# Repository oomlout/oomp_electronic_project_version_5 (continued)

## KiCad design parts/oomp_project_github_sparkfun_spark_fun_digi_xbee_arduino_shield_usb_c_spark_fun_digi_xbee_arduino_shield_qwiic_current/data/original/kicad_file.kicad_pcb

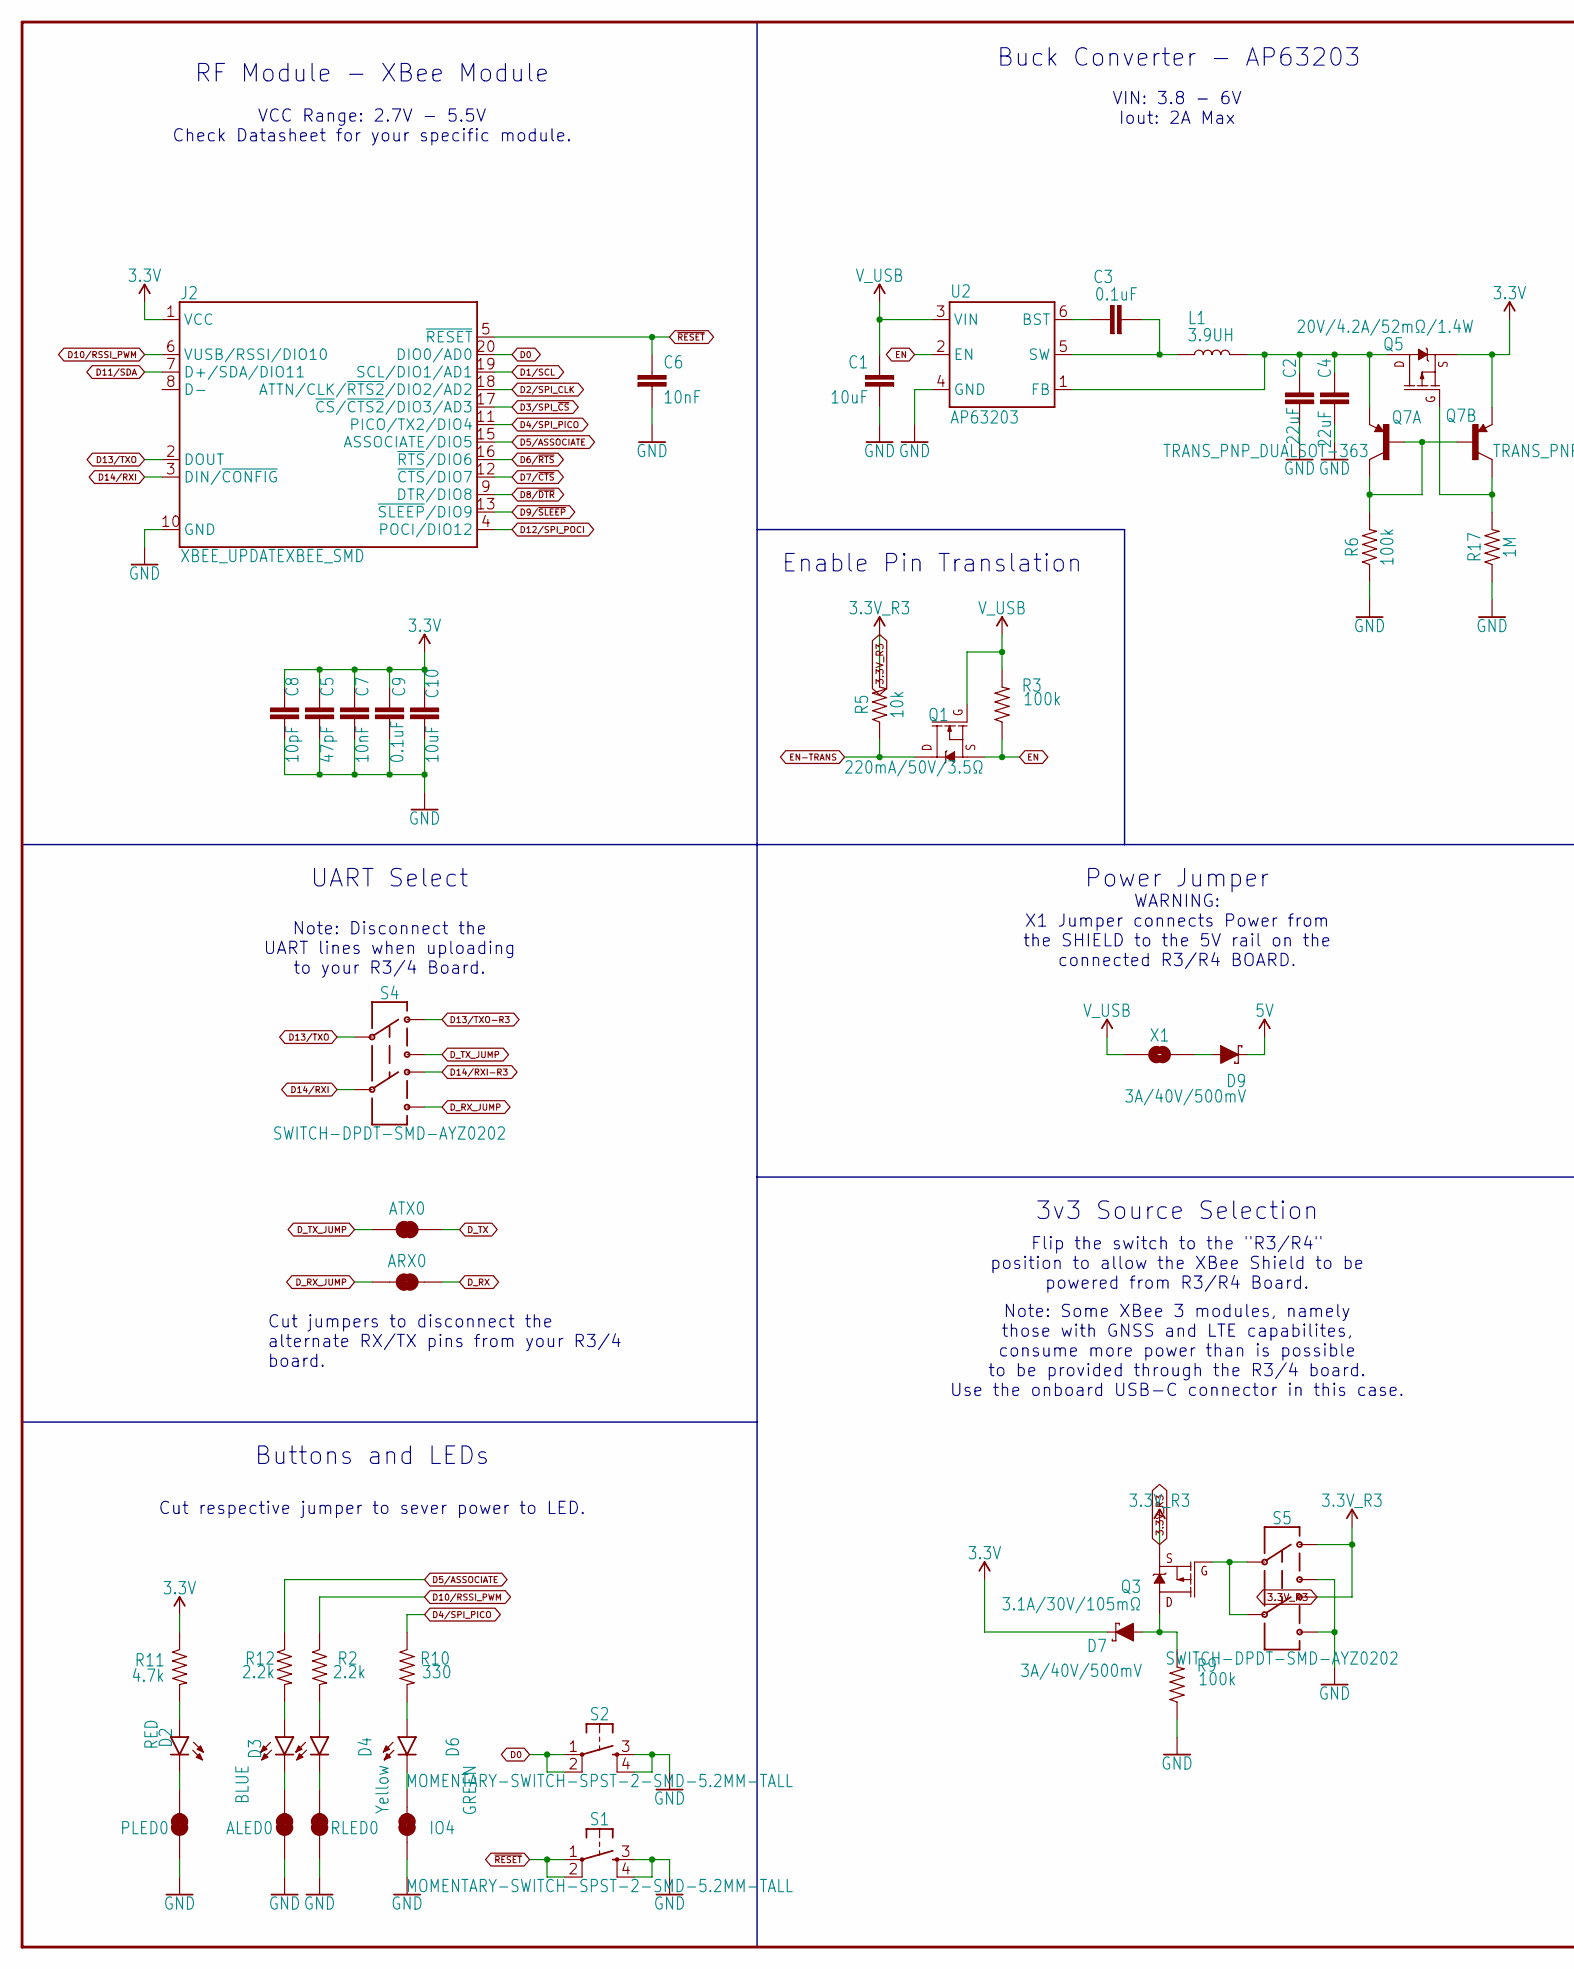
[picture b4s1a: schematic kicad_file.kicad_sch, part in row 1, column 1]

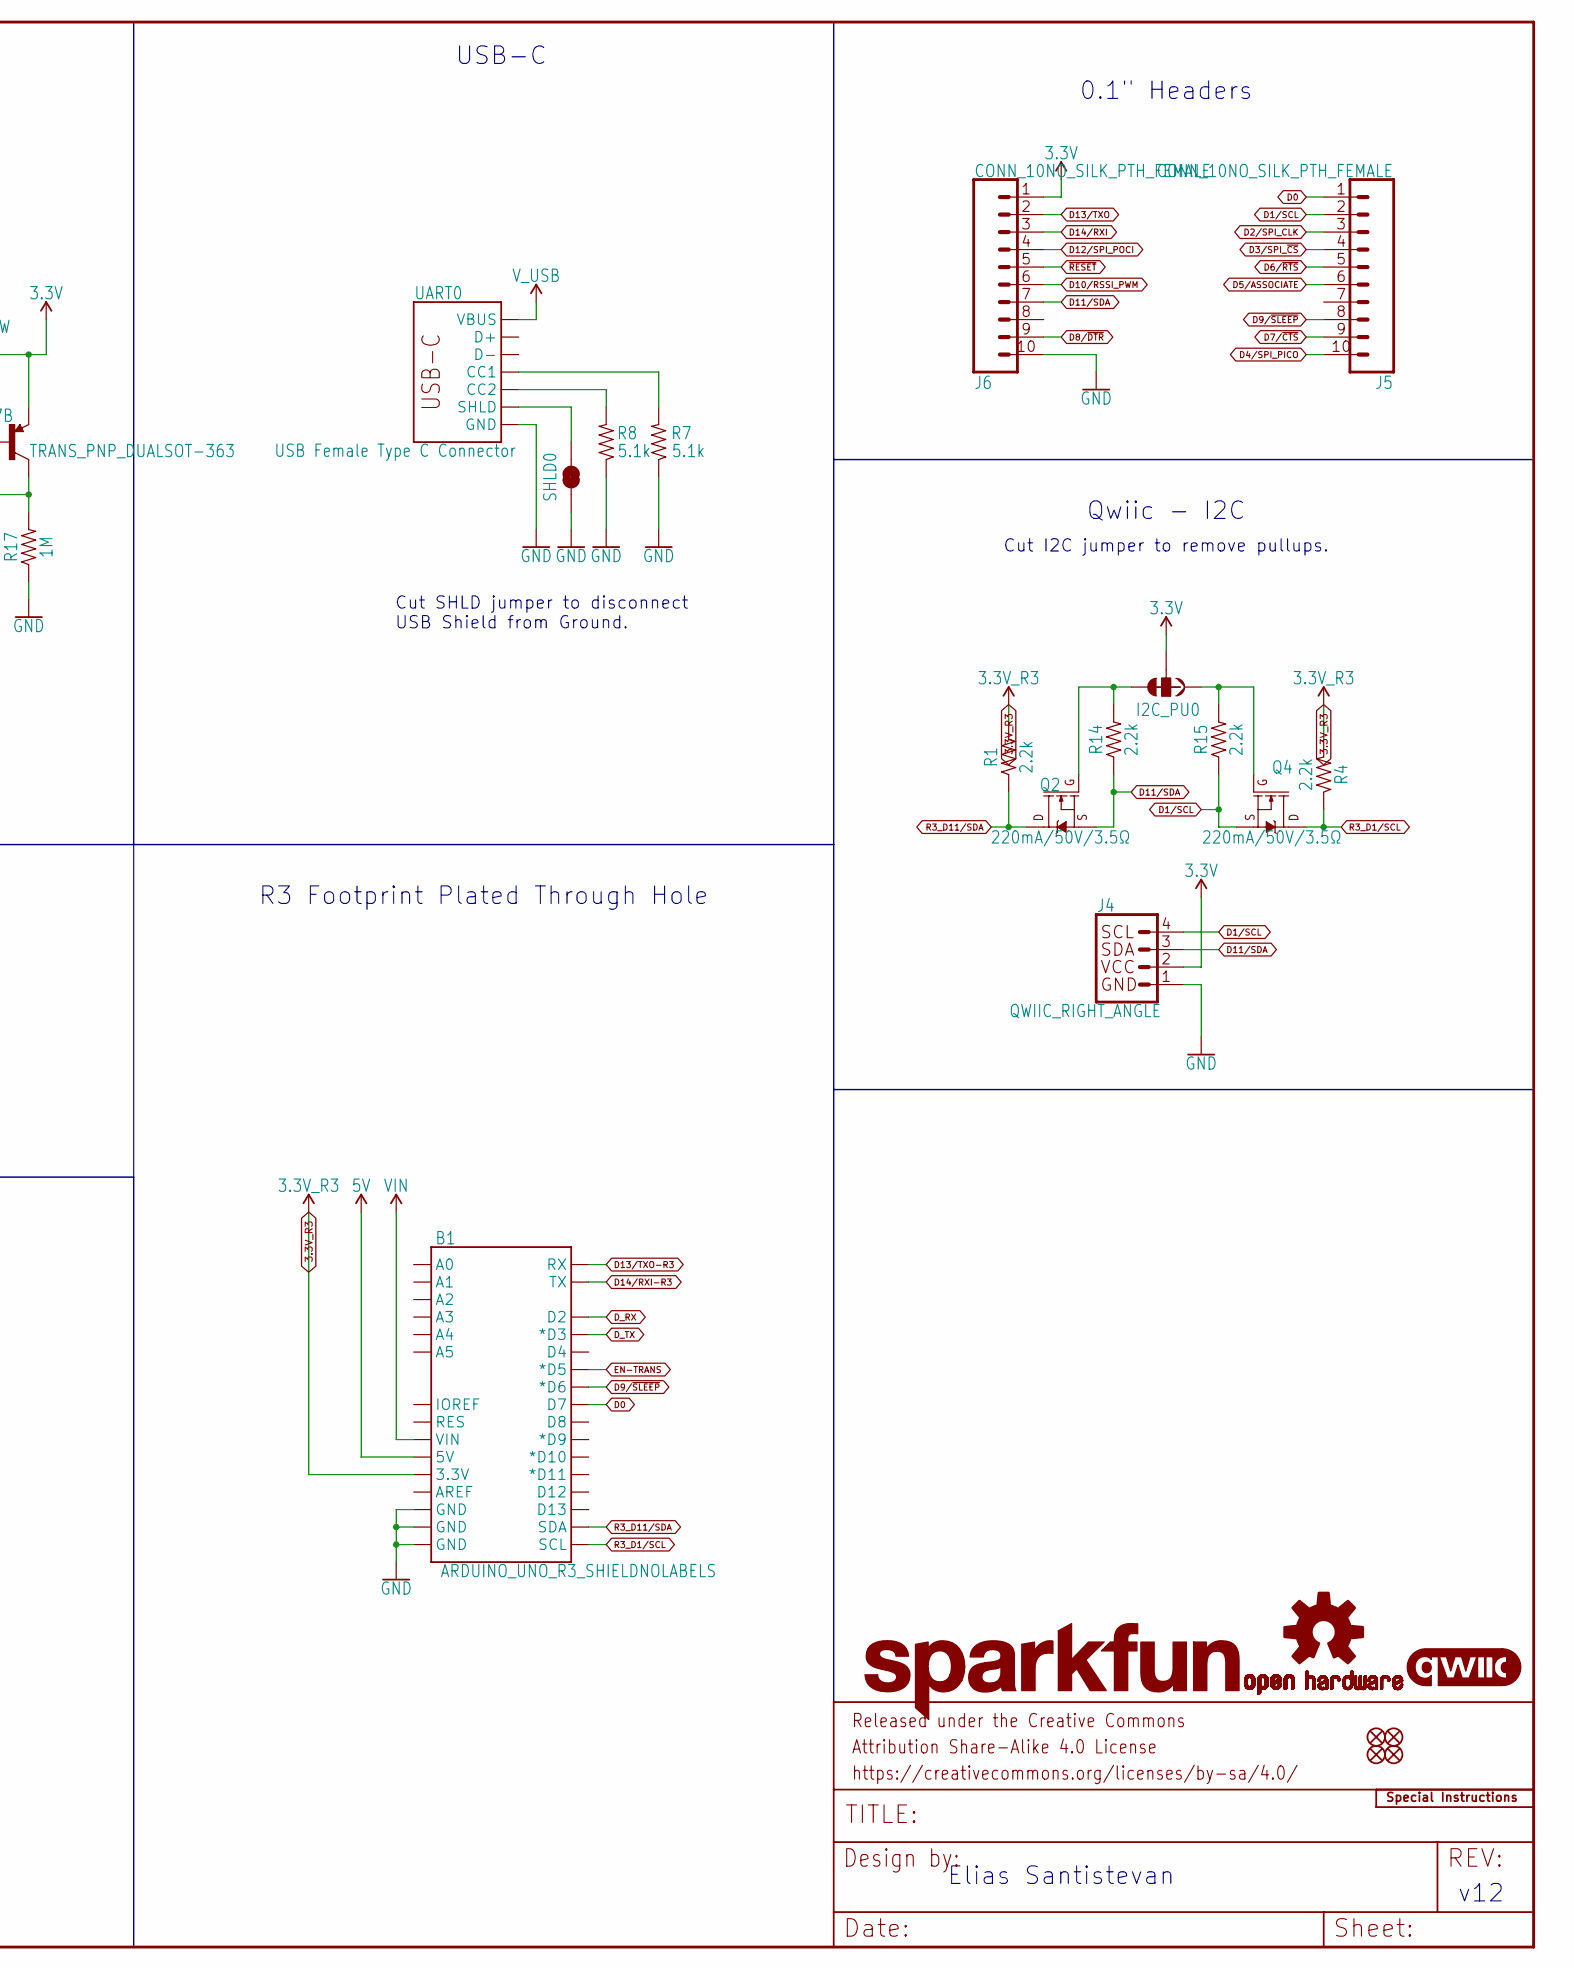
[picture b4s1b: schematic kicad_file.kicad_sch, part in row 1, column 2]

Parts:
ALED0: JUMPER-SMT_2_NC_TRACE_SILK; SMT-JUMPER_2_NC_TRACE_SILK
ARX0: JUMPER-SMT_2_NC_TRACE_SILK; SMT-JUMPER_2_NC_TRACE_SILK
ATX0: JUMPER-SMT_2_NC_TRACE_SILK; SMT-JUMPER_2_NC_TRACE_SILK
B1: ARDUINO_UNO_R3_SHIELDNOLABELS; UNO_R3_SHIELD_NOLABELS
C1: 10uF; 1210
C2, C4: 22uF; 0603
C3, C9: 0.1uF; 0603
C5: 47pF; 0603
C6, C7: 10nF; 0603
C8: 10pF; 0603
C10: 10uF; 0603
D2: RED; LED-0603
D3: BLUE; LED-0603
D4: Yellow; LED-0603
D6: GREEN; LED-0603
D7, D9: 3A/40V/500mV; SMA-DIODE
FD1, FD2, FD3, FD4: FIDUCIAL1X2; FIDUCIAL-1X2
FRAME1: FRAME-LEDGER; CREATIVE_COMMONS
I2C_PU0: JUMPER-SMT_3_2-NC_TRACE_SILK; SMT-JUMPER_3_2-NC_TRACE_SILK
IO4: JUMPER-SMT_2_NC_TRACE_SILK; SMT-JUMPER_2_NC_TRACE_SILK
J2: XBEE_UPDATEXBEE_SMD; XBEE3-SMD
J4: QWIIC_RIGHT_ANGLE; JST04_1MM_RA
J5, J6: CONN_10NO_SILK_PTH_FEMALE; 1X10_NO_SILK
L1: 3.9UH; INDUCTOR_3.9UH
LOGO1: SFE_LOGO_NAMEBLANK; BLANK
LOGO2: OSHW-LOGOS; OSHW-LOGO-S
LOGO3: QWIIC_LOGO_4MM; QWIIC_4MM
LOGO4: SPECIAL_INSTRUCTIONS-ORDERING; ORDERING_INSTRUCTIONS
PLED0: JUMPER-SMT_2_NC_TRACE_SILK; SMT-JUMPER_2_NC_TRACE_SILK
Q1, Q2, Q4: 220mA/50V/3.5Ω; SOT23-3
Q3: 3.1A/30V/105mΩ; SOT23-3
Q5: 20V/4.2A/52mΩ/1.4W; SOT23-3
Q7: TRANS_PNP_DUALSOT-363; SOT363_PHILIPS
R1, R2, R4, R12, R14, R15: 2.2k; 0603
R3, R6, R9: 100k; 0603
R5: 10k; 0603
R7, R8: 5.1k; 0603
R10: 330; 0603
R11: 4.7k; 0603
R17: 1M; 0603
RLED0: JUMPER-SMT_2_NC_TRACE_SILK; SMT-JUMPER_2_NC_TRACE_SILK
S1, S2: MOMENTARY-SWITCH-SPST-2-SMD-5.2MM-TALL; TACTILE_SWITCH_SMD_5.2MM
S4, S5: SWITCH-DPDT-SMD-AYZ0202; SWITCH_DPDT_SMD_AYZ0202
SHLD0: JUMPER-SMT_2_NC_TRACE_SILK; SMT-JUMPER_2_NC_TRACE_SILK
U2: AP63203; SOT23-6
UART0: USB Female Type C Connector; USB-C-16P-4LAYER-ISOLATED
X1: JUMPER-SMT_2_NO_SILK; SMT-JUMPER_2_NO_SILK

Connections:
3.3V: C5.1, C7.1, C8.1, C9.1, C10.1, D7.C, I2C_PU0.2, J2.1 (VCC), J4.2, J6.1, Q5.2 (S), Q7.4 (E), R11.1
3.3V_R3: B1.3.3V, Q3.2 (S), R1.2, R4.2, R5.2, S5.3, S5.6
3.3V_VREG: C2.1, C4.1, L1.P$2 (2), Q5.3 (D), Q7.1 (E), U2.1 (FB)
5V: B1.5V, D9.C
D0: B1.D7, J2.20 (DIO0/AD0), J5.1, S2.1, S2.2
D1/SCL: J2.19 (SCL/DIO1/AD1), J4.4, J5.2, Q4.2 (S), R15.1
D2/SPI_CLK: J2.18 (ATTN/CLK/~RTS2/DIO2/AD2), J5.3
D3/SPI_~CS: J2.17 (~CS/~CTS2/DIO3/AD3), J5.4
D4/SPI_PICO: J2.11 (PICO/TX2/DIO4), J5.10, R10.1
D5/ASSOCIATE: J2.15 (ASSOCIATE/DIO5), J5.6, R12.1
D6/~RTS: J2.16 (~RTS/DIO6), J5.5
D7/~CTS: J2.12 (~CTS/DIO7), J5.9
D8/~DTR: J2.9 (DTR/DIO8), J6.9
D9/~SLEEP: B1.D6 (*D6), J2.13 (~SLEEP/DIO9), J5.8
D10/RSSI_PWM: J2.6 (VUSB/RSSI/DIO10), J6.6, R2.1
D11/SDA: J2.7 (D+/SDA/DIO11), J4.3, J6.7, Q2.2 (S), R14.1
D12/SPI_POCI: J2.4 (POCI/DIO12), J6.4
D13/TXO: J2.2 (DOUT), J6.2, S4.2
D13/TXO-R3: B1.RX, S4.3
D14/RXI: J2.3 (DIN/~CONFIG), J6.3, S4.5
D14/RXI-R3: B1.TX, S4.6
D_RX: ARX0.2, B1.D2
D_RX_JUMP: ARX0.1, S4.4
D_TX: ATX0.2, B1.D3 (*D3)
D_TX_JUMP: ATX0.1, S4.1
EN: Q1.2 (S), R3.1, U2.2 (EN)
EN-TRANS: B1.D5 (*D5), Q1.3 (D), R5.1
GND: ALED0.1, B1.GND@0 (GND), B1.GND@1 (GND), B1.GND@2 (GND), C1.2, C2.2, C4.2, C5.2, C6.2, C7.2, C8.2, C9.2, C10.2, IO4.1, J2.10 (GND), J4.1, J6.10, PLED0.1, R6.1, R7.1, R8.1, R9.1, R17.1, RLED0.1, S1.3, S1.4, S2.3, S2.4, S5.1, S5.4, SHLD0.1, U2.4 (GND), UART0.GND, UART0.GND2 (GND)
unnamed: C3.1, U2.6 (BST)
unnamed: D4.A, R2.2
unnamed: D4.C, RLED0.2
unnamed: D6.A, R10.2
unnamed: R8.2, UART0.B5 (CC2)
unnamed: R7.2, UART0.A5 (CC1)
unnamed: D2.A, R11.2
unnamed: C3.2, L1.P$1 (1), U2.5 (SW)
unnamed: D9.A, X1.2
unnamed: I2C_PU0.1, Q4.1 (G), R15.2
unnamed: I2C_PU0.3, Q2.1 (G), R14.2
unnamed: D3.A, R12.2
unnamed: D7.A, Q3.3 (D), R9.2
unnamed: D6.C, IO4.2
unnamed: Q7.2 (B), Q7.5 (B), Q7.6 (C), R6.2
unnamed: Q5.1 (G), Q7.3 (C), R17.2
unnamed: ALED0.2, D3.C
unnamed: D2.C, PLED0.2
unnamed: Q3.1 (G), S5.2, S5.5
R3_D1/SCL: B1.SCL, Q4.3 (D), R4.1
R3_D11/SDA: B1.SDA, Q2.3 (D), R1.1
SHLD: SHLD0.2, UART0.SHLD1 (SHLD), UART0.SHLD2 (SHLD), UART0.SHLD3 (SHLD), UART0.SHLD4 (SHLD), UART0.SHLD5 (SHLD), UART0.SHLD6 (SHLD), UART0.SHLD7 (SHLD), UART0.SHLD8 (SHLD)
VIN: B1.VIN
V_USB: C1.1, Q1.1 (G), R3.2, U2.3 (VIN), UART0.VBUS1 (VBUS), UART0.VBUS2 (VBUS), X1.1
~RESET: C6.1, J2.5 (~RESET), J6.5, S1.1, S1.2

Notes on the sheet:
USB-C
0.1" Headers
R3 Footprint Plated Through Hole
Flip the switch to the "R3/R4" position to allow the XBee Shield to be powered from R3/R4 Board.
Cut respective jumper to sever power to LED.
Buck Converter - AP63203
Cut jumpers to disconnect the alternate RX/TX pins from your R3/4 board.
Note: Disconnect the UART lines when uploading to your R3/4 Board.
UART Select
VIN: 3.8 - 6V Iout: 2A Max
Power Jumper
Buttons and LEDs
3v3 Source Selection
Note: Some XBee 3 modules, namely those with GNSS and LTE capabilites, consume more power than is possible to be provided through the R3/4 board. Use the onboard USB-C connector in this case.
RF Module - XBee Module
Enable Pin Translation
Cut I2C jumper to remove pullups.
v12
Elias Santistevan
Qwiic - I2C
VCC Range: 2.7V - 5.5V Check Datasheet for your specific module.
WARNING: X1 Jumper connects Power from the SHIELD to the 5V rail on the connected R3/R4 BOARD.
Cut SHLD jumper to disconnect USB Shield from Ground.

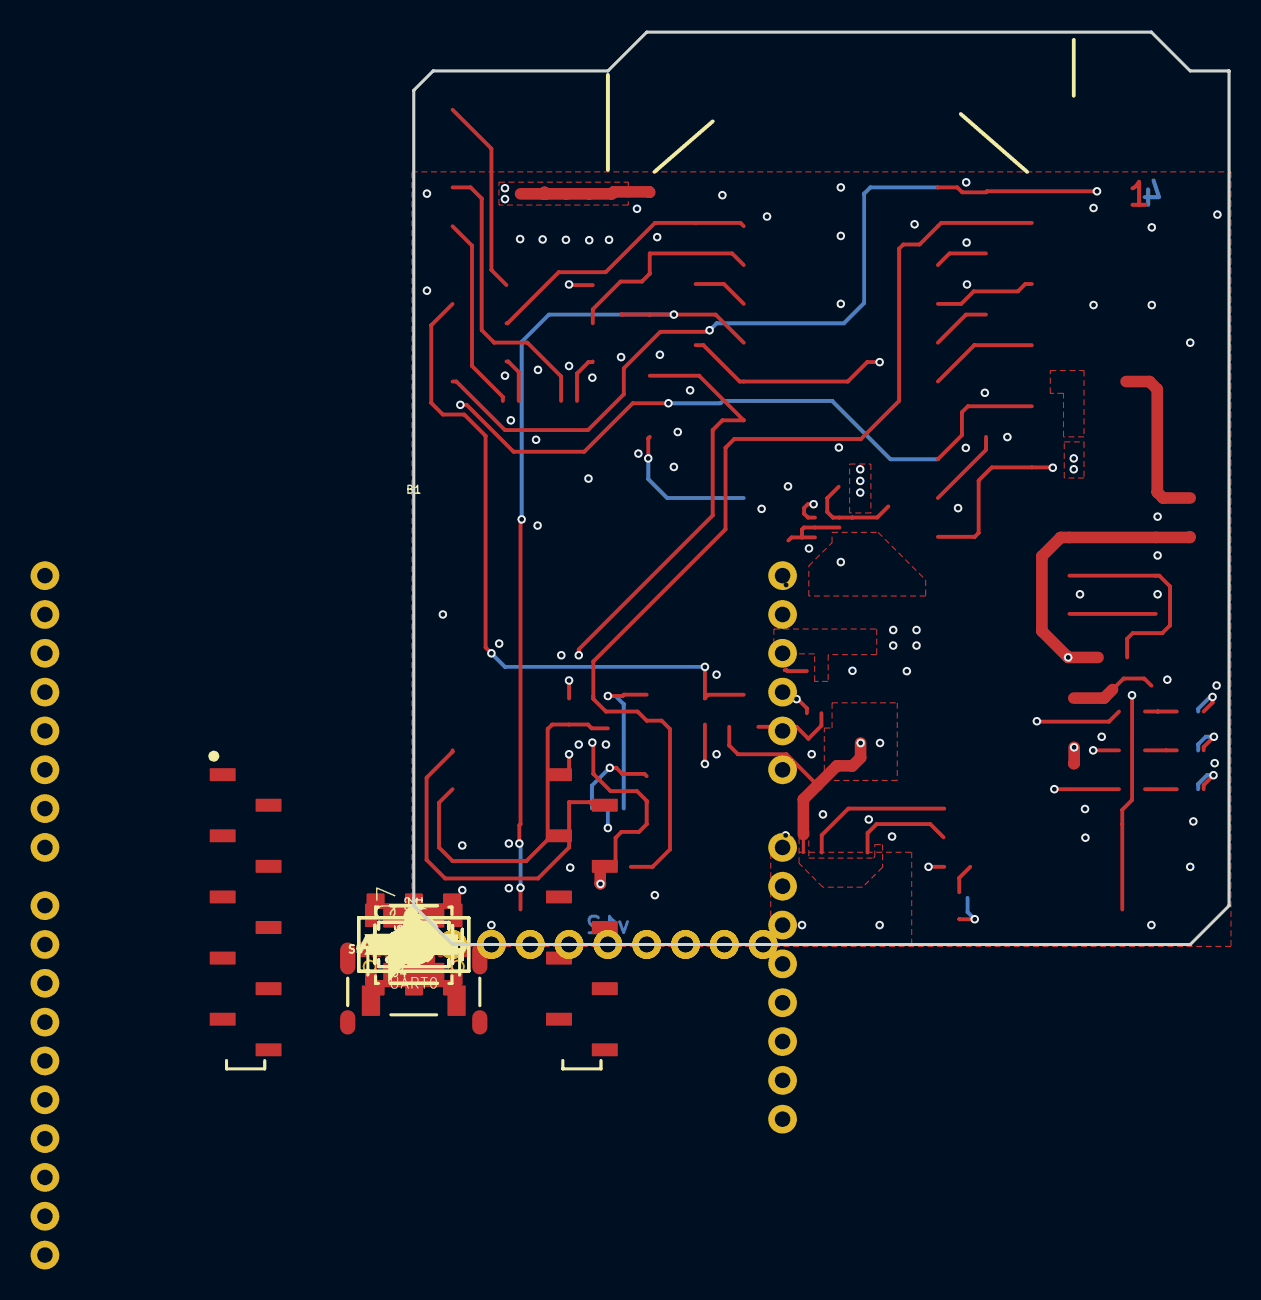
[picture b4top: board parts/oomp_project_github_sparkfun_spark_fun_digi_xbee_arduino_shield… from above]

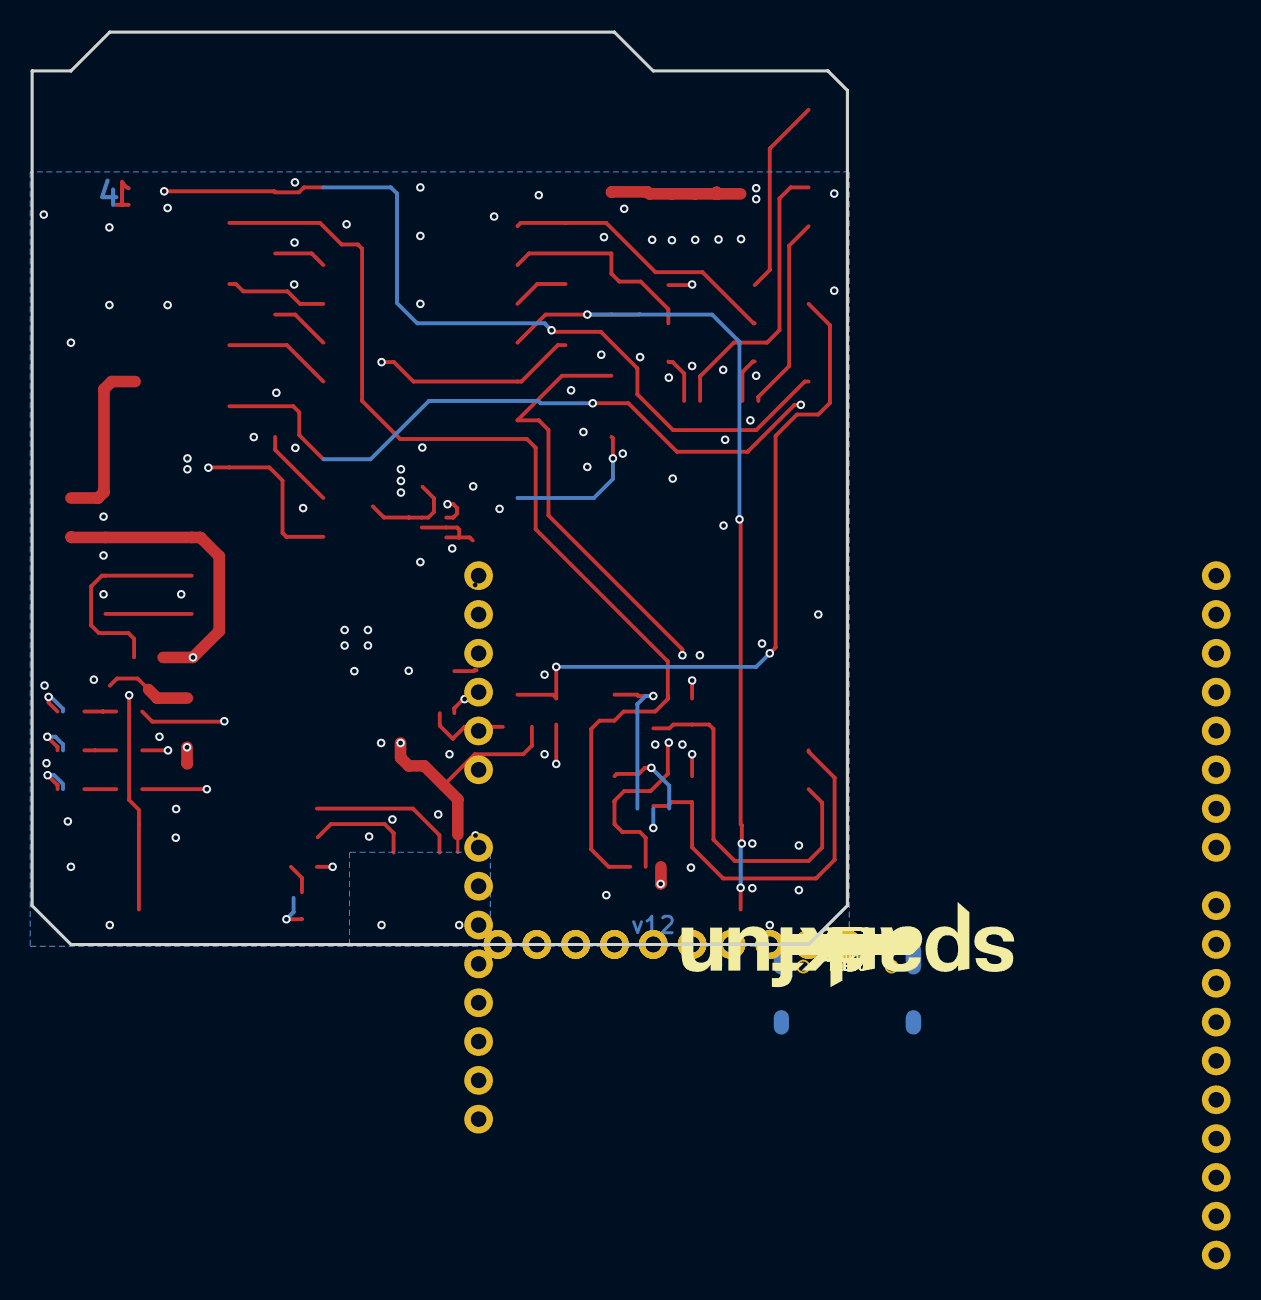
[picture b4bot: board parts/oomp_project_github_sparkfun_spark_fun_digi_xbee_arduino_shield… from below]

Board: 4 copper layers, 53.3 x 59.7 mm, 163 parts (51 on the bottom side), 52 nets.

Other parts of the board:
U$1: RSSI31
U$2: PWR29
U$3, U$56: #SDA#10
U$4: #SHLD#36
U$5, U$9: #NC#1
U$6: #D3#AD3#23
U$7, U$10: #NC#3
U$8: ##DTR##27
U$11: #D1#AD1#8
U$12: ##CTS##28
U$13: #D8##DTR##27
U$14: #RSSI#D10#17
U$15: #SDA#D11#9
U$16: ##RST##15
U$17: #POCI#D12#24
U$18: #RXI#D14#15
U$19: #D2#AD2#19
U$20: #D6##RTS##25
U$21, U$32: #TXO#8
U$22: #TXO#D13#13
U$23: VIN5
U$24: #SCL#7
U$25, U$29, U$41, U$50, U$53, U$63, U$76, U$82: #GND#0
U$26: #I2C#33
U$27, U$33: #RXI#7
U$28: DRX52
U$30: #RST#30
U$31: #PICO#27
U$34: DTX53
U$35: #D5#ASSOC#25
U$36: #D9##SLP##28
U$37: #D7##CTS##26
U$38: #D4#PICO#25
U$39, U$66: #5V#5
U$40: D03
U$42: DLINE45
U$43: #X1#10
U$44, U$47, U$77, U$84: #3V3#1
U$45: #POCI#32
U$46: SHIELD55
U$48: UART44
U$49: #ALED#21
U$51: #RLED#22
U$52: #PLED#20
U$54, U$87: ##RST##13
U$55: #RSSI#16
U$57: #ASSOC#28
U$58: ##RTS##14
U$59: ##CS##26
U$60: #SCLK#33
U$61: SFE_LOGO_FLAME_.2
U$62: SFE_LOGO_NAME_.2
U$64: #SCL#9
U$65: #D0#3
U$67: #SDA#9
U$68: ##SLP##28
U$69: R3#R455
U$70: #SCL#13
U$71, U$86: #DRX#56
U$72, U$89: #DTX#57
U$73: #TXO#61
U$74: ASC32
U$75: POWER49
U$78: #D0#AD0#18
U$79: ARDUINO1345
U$80: XBEE340
U$81: SHIELD1346
U$83: #EN#15
U$85: #RXI#60
U$88: #VIN#4
U$90: #XBEE_DIO0#62
U$91: #UART#4048234
U$92: #XBEE_DIO9#62
U$93: #IOLED#5
U$94: IO49
U$95: SOURCE54
U$96: USB#C58

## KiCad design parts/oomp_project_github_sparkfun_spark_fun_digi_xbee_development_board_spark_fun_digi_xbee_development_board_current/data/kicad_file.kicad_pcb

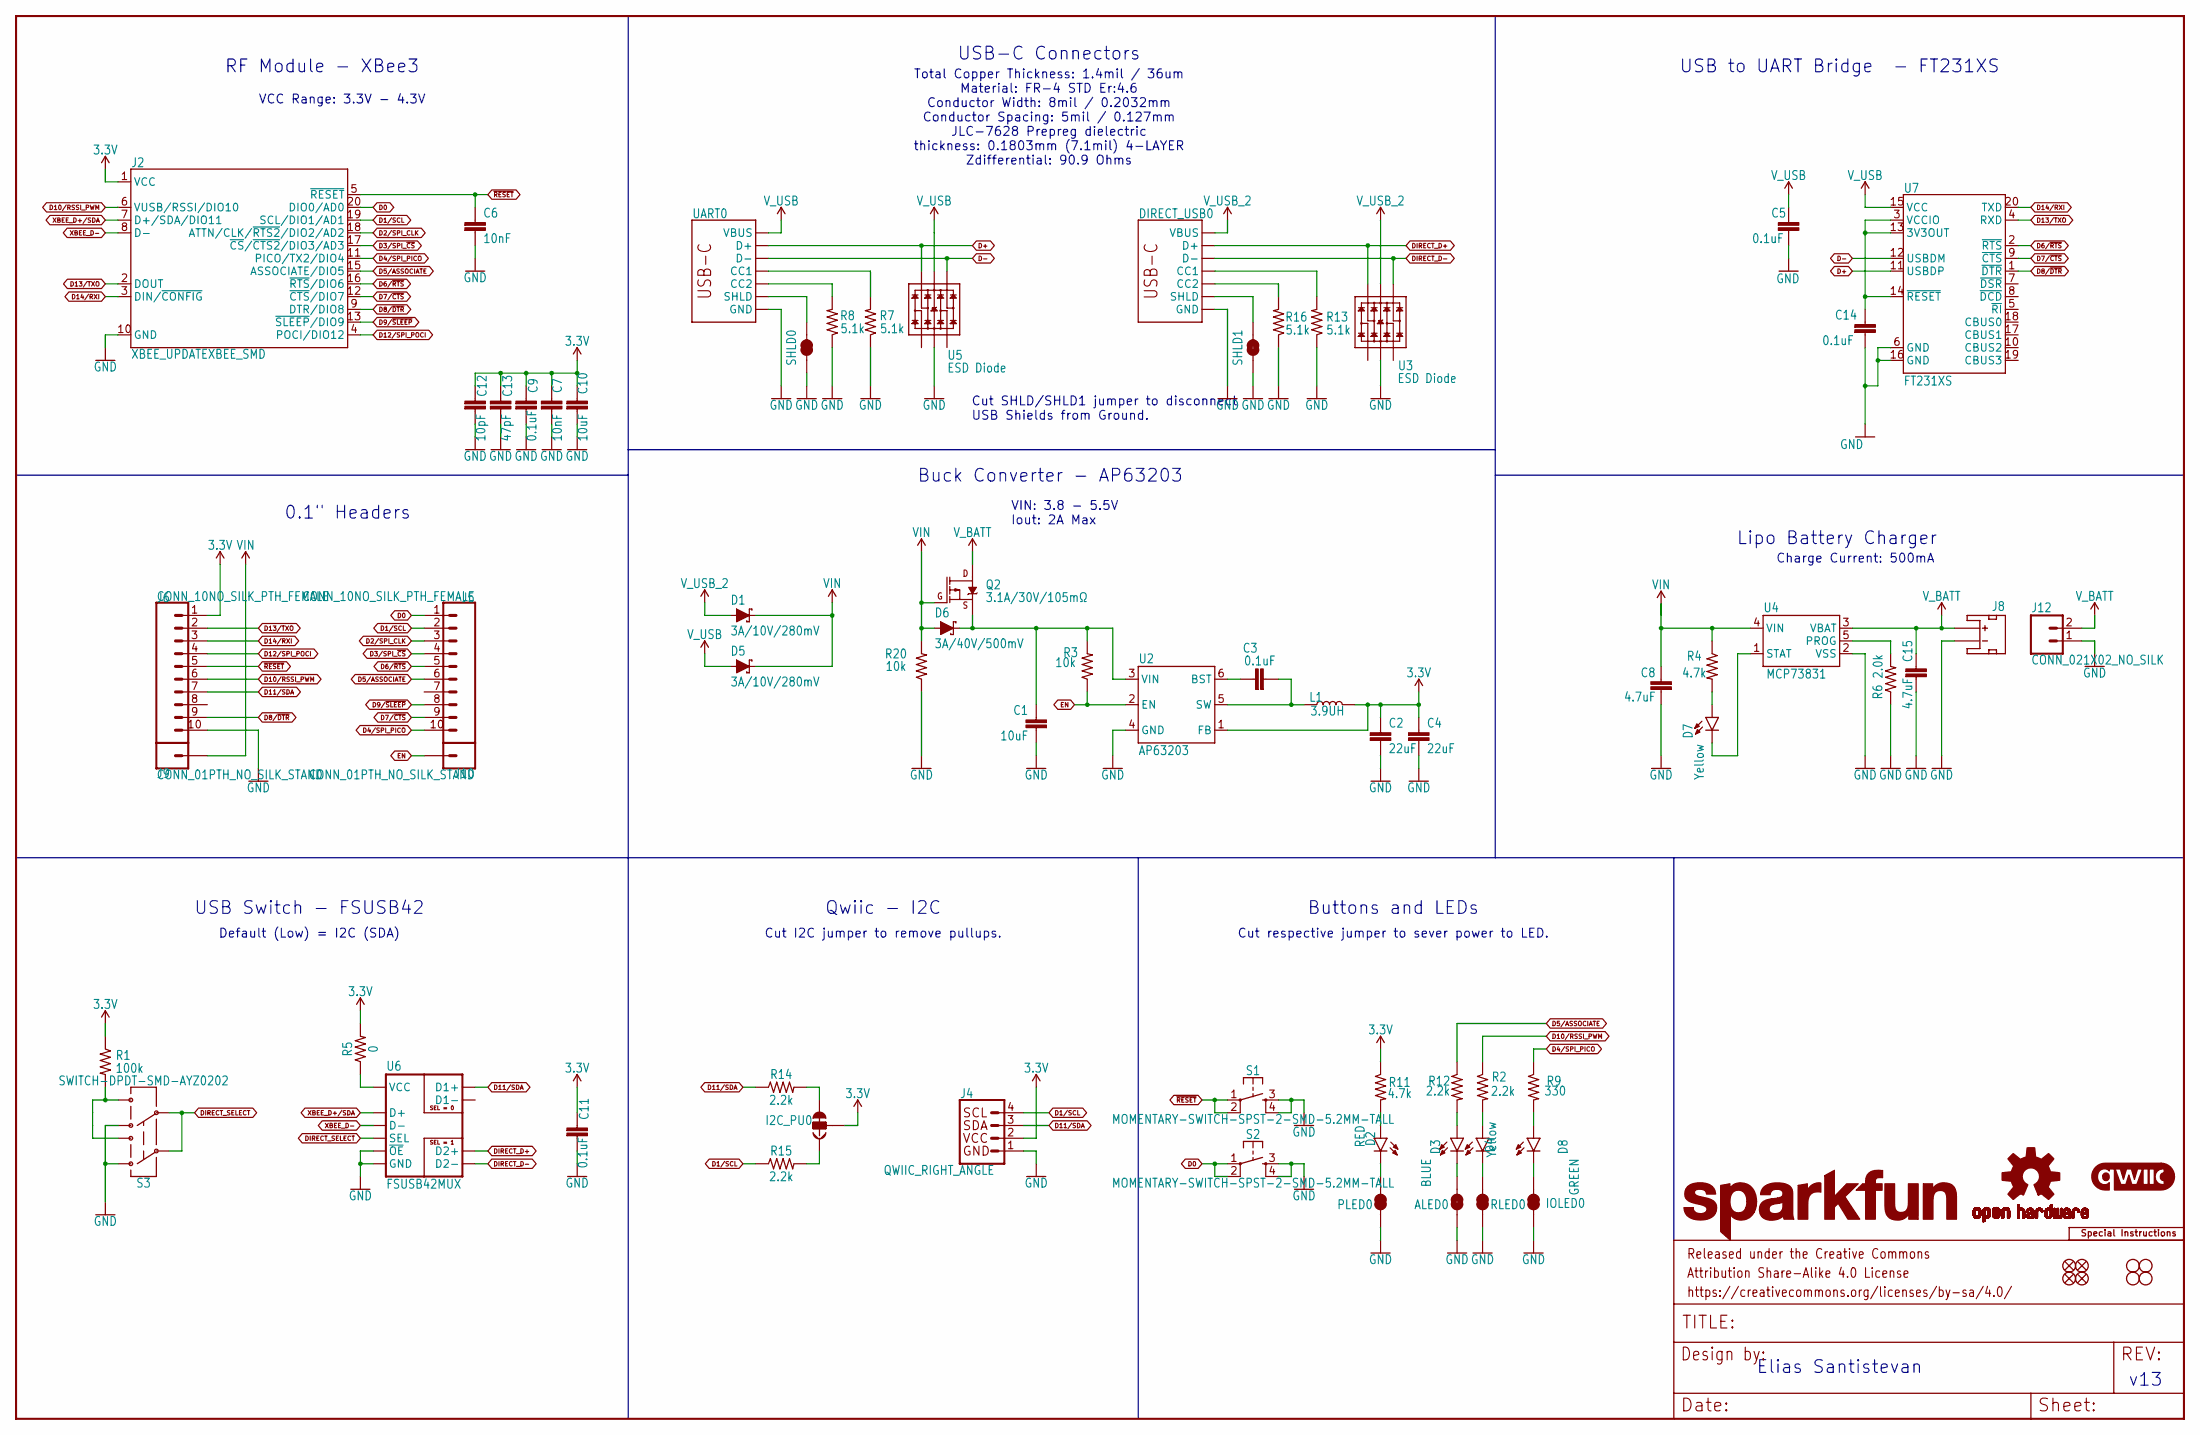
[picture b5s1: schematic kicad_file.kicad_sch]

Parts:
ALED0: JUMPER-SMT_2_NC_TRACE_SILK; SMT-JUMPER_2_NC_TRACE_SILK
C1: 10uF; 1210
C2, C4: 22uF; 0603
C3, C5, C9, C11, C14: 0.1uF; 0603
C6, C7: 10nF; 0603
C8, C15: 4.7uF; 0603
C10: 10uF; 0603
C12: 10pF; 0603
C13: 47pF; 0603
D1, D5: 3A/10V/280mV; SOD-323
D2: RED; LED-0603
D3: BLUE; LED-0603
D4, D7: Yellow; LED-0603
D6: 3A/40V/500mV; SMA-DIODE
D8: GREEN; LED-0603
DIRECT_USB0: USB Female Type C Connector; USB-C-16P-4LAYER-ISOLATED
FD1, FD2, FD3, FD4: FIDUCIAL1X2; FIDUCIAL-1X2
FRAME1: FRAME-LEDGER; CREATIVE_COMMONS
H1, H2, H3, H4: STAND-OFFTIGHT; STAND-OFF-TIGHT
I2C_PU0: JUMPER-SMT_3_2-NC_TRACE_SILK; SMT-JUMPER_3_2-NC_TRACE_SILK
IOLED0: JUMPER-SMT_2_NC_TRACE_SILK; SMT-JUMPER_2_NC_TRACE_SILK
J2: XBEE_UPDATEXBEE_SMD; XBEE3-SMD
J4: QWIIC_RIGHT_ANGLE; JST04_1MM_RA
J5, J6: CONN_10NO_SILK_PTH_FEMALE; 1X10_NO_SILK
J8: JST_2MM_MALE; JST-2-SMD
J9, J10: CONN_01PTH_NO_SILK_STAND; 1X01_NO_SILK_STAND
J12: CONN_021X02_NO_SILK; 1X02_NO_SILK
L1: 3.9UH; INDUCTOR_3.9UH
LOGO1: SFE_LOGO_NAME.2_INCH; SFE_LOGO_NAME_.2
LOGO2: OSHW-LOGOS; OSHW-LOGO-S
LOGO3: QWIIC_LOGO_5MM; QWIIC_5MM
LOGO5: SPECIAL_INSTRUCTIONS-ORDERING; ORDERING_INSTRUCTIONS
PLED0: JUMPER-SMT_2_NC_TRACE_SILK; SMT-JUMPER_2_NC_TRACE_SILK
Q2: 3.1A/30V/105mΩ; SOT23-3
R1: 100k; 0603
R2, R12, R14, R15: 2.2k; 0603
R3, R20: 10k; 0603
R4, R11: 4.7k; 0603
R5: 0; 0603
R6: 2.0k; 0603
R7, R8, R13, R16: 5.1k; 0603
R9: 330; 0603
RLED0: JUMPER-SMT_2_NC_TRACE_SILK; SMT-JUMPER_2_NC_TRACE_SILK
S1, S2: MOMENTARY-SWITCH-SPST-2-SMD-5.2MM-TALL; TACTILE_SWITCH_SMD_5.2MM
S3: SWITCH-DPDT-SMD-AYZ0202; SWITCH_DPDT_SMD_AYZ0202
SHLD0, SHLD1: JUMPER-SMT_2_NC_TRACE_SILK; SMT-JUMPER_2_NC_TRACE_SILK
U2: AP63203; SOT23-6
U3, U5: ESD Diode; SOT-23-6
U4: MCP73831; SOT23-5
U6: FSUSB42MUX; MSOP10
U7: FT231XS; SSOP20_L
UART0: USB Female Type C Connector; USB-C-16P-4LAYER-ISOLATED

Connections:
3.3V: C2.1, C4.1, C7.1, C9.1, C10.1, C11.1, C12.1, C13.1, I2C_PU0.2, J2.1 (VCC), J4.2, J6.1, L1.P$2 (2), R1.1, R5.2, R11.1, U2.1 (FB)
ALED: ALED0.2, D3.C
D0: J2.20 (DIO0/AD0), J5.1, S2.1, S2.2
D1/SCL: J2.19 (SCL/DIO1/AD1), J4.4, J5.2, R15.1
D2/SPI_CLK: J2.18 (ATTN/CLK/~RTS2/DIO2/AD2), J5.3
D3/SPI_~CS: J2.17 (~CS/~CTS2/DIO3/AD3), J5.4
D4/SPI_PICO: J2.11 (PICO/TX2/DIO4), J5.10, R9.1
D5/ASSOCIATE: J2.15 (ASSOCIATE/DIO5), J5.6, R12.1
D6/~RTS: J2.16 (~RTS/DIO6), J5.5, U7.2 (~RTS)
D7/~CTS: J2.12 (~CTS/DIO7), J5.9, U7.9 (~CTS)
D8/~DTR: J2.9 (DTR/DIO8), J6.9, U7.1 (~DTR)
D9/~SLEEP: J2.13 (~SLEEP/DIO9), J5.8
D10/RSSI_PWM: J2.6 (VUSB/RSSI/DIO10), J6.6, R2.1
D11/SDA: J4.3, J6.7, R14.1, U6.7 (D1+)
D12/SPI_POCI: J2.4 (POCI/DIO12), J6.4
D13/TXO: J2.2 (DOUT), J6.2, U7.4 (RXD)
D14/RXI: J2.3 (DIN/~CONFIG), J6.3, U7.20 (TXD)
D+: U5.6 (IO4), U7.11 (USBDP), UART0.A6 (D+), UART0.B6 (D+)
D-: U5.4 (IO3), U7.12 (USBDM), UART0.A7 (D-), UART0.B7 (D-)
DIRECT_D+: DIRECT_USB0.A6 (D+), DIRECT_USB0.B6 (D+), U3.6 (IO4), U6.9 (D2+)
DIRECT_D-: DIRECT_USB0.A7 (D-), DIRECT_USB0.B7 (D-), U3.4 (IO3), U6.8 (D2-)
DIRECT_SELECT: S3.2, S3.5, U6.2 (SEL)
EN: J10.1, R3.1, U2.2 (EN)
FIRMWARE: R1.2, S3.1, S3.4
GND: ALED0.1, C1.2, C2.2, C4.2, C5.2, C6.2, C7.2, C8.2, C9.2, C10.2, C11.2, C12.2, C13.2, C14.2, C15.2, DIRECT_USB0.GND, DIRECT_USB0.GND2 (GND), IOLED0.1, J2.10 (GND), J4.1, J6.10, J8.1 (-), J12.1, PLED0.1, R6.1, R7.1, R8.1, R13.1, R16.1, R20.1, RLED0.1, S1.3, S1.4, S2.3, S2.4, S3.3, S3.6, SHLD0.1, SHLD1.1, U2.4 (GND), U3.2 (VSS), U4.2 (VSS), U5.2 (VSS), U6.5 (GND), U6.10 (~OE), U7.6 (GND), U7.16 (GND), UART0.GND, UART0.GND2 (GND)
IOLED: D8.C, IOLED0.2
unnamed: C3.1, U2.6 (BST)
unnamed: D4.A, R2.2
unnamed: R5.1, U6.1 (VCC)
unnamed: R8.2, UART0.B5 (CC2)
unnamed: R7.2, UART0.A5 (CC1)
unnamed: R6.2, U4.5 (PROG)
unnamed: D2.A, R11.2
unnamed: C3.2, L1.P$1 (1), U2.5 (SW)
unnamed: D7.C, U4.1 (STAT)
unnamed: D7.A, R4.2
unnamed: I2C_PU0.3, R14.2
unnamed: D3.A, R12.2
unnamed: I2C_PU0.1, R15.2
unnamed: DIRECT_USB0.B5 (CC2), R16.2
unnamed: C1.1, D6.C, Q2.2 (S), R3.2, U2.3 (VIN)
unnamed: DIRECT_USB0.A5 (CC1), R13.2
unnamed: D8.A, R9.2
unnamed: C14.1, U7.3 (VCCIO), U7.13 (3V3OUT), U7.14 (~RESET)
PLED: D2.C, PLED0.2
RLED: D4.C, RLED0.2
SHLD: SHLD0.2, UART0.SHLD1 (SHLD), UART0.SHLD2 (SHLD), UART0.SHLD3 (SHLD), UART0.SHLD4 (SHLD), UART0.SHLD5 (SHLD), UART0.SHLD6 (SHLD), UART0.SHLD7 (SHLD), UART0.SHLD8 (SHLD)
SHLD1: DIRECT_USB0.SHLD1 (SHLD), DIRECT_USB0.SHLD2 (SHLD), DIRECT_USB0.SHLD3 (SHLD), DIRECT_USB0.SHLD4 (SHLD), DIRECT_USB0.SHLD5 (SHLD), DIRECT_USB0.SHLD6 (SHLD), DIRECT_USB0.SHLD7 (SHLD), DIRECT_USB0.SHLD8 (SHLD), SHLD1.2
VIN: C8.1, D1.C, D5.C, D6.A, J9.1, Q2.1 (G), R4.1, R20.2, U4.4 (VIN)
V_BATT: C15.1, J8.2 (+), J12.2, Q2.3 (D), U4.3 (VBAT)
V_USB: C5.1, D5.A, U5.5 (VCC), U7.15 (VCC), UART0.VBUS1 (VBUS), UART0.VBUS2 (VBUS)
V_USB_2: D1.A, DIRECT_USB0.VBUS1 (VBUS), DIRECT_USB0.VBUS2 (VBUS), U3.5 (VCC)
XBEE_D+/SDA: J2.7 (D+/SDA/DIO11), U6.3 (D+)
XBEE_D-: J2.8 (D-), U6.4 (D-)
~RESET: C6.1, J2.5 (~RESET), J6.5, S1.1, S1.2

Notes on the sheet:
Charge Current: 500mA
Qwiic - I2C
v13
Buck Converter - AP63203
Default (Low) = I2C (SDA)
Buttons and LEDs
VCC Range: 3.3V - 4.3V
Lipo Battery Charger
USB-C Connectors
VIN: 3.8 - 5.5V Iout: 2A Max
USB Switch - FSUSB42
Cut SHLD/SHLD1 jumper to disconnect USB Shields from Ground.
Total Copper Thickness: 1.4mil / 36um Material: FR-4 STD Er:4.6 Conductor Width: 8mil / 0.2032mm Conductor Spacing: 5mil / 0.127mm JLC-7628 Prepreg dielectric thickness: 0.1803mm (7.1mil) 4-LAYER Zdifferential: 90.9 Ohms
USB to UART Bridge - FT231XS
Elias Santistevan
0.1" Headers
Cut respective jumper to sever power to LED.
Cut I2C jumper to remove pullups.
RF Module - XBee3
